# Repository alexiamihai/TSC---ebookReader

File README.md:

# OpenBook - Cititor ePaper cu ESP32-C6

## Prezentare

OpenBook este un eBook reader simplu si eficient, gandit pentru cei care vor o experienta de lectura fara distrageri. Proiectat in jurul microcontrollerului ESP32-C6, dispozitivul vine cu un ecran e-paper de 7.8 inch, ideal pentru afisarea clara a textelor in orice conditii de lumina.

Alimentarea se face printr-o baterie Li-Po de 3.7V, cu incarcare prin USB-C, iar navigarea printre pagini se realizeaza cu ajutorul butoanelor fizice, pentru o interactiune directa si intuitiva. In plus, cititorul dispune de un slot microSD pentru stocarea cartilor, un senzor BME680 pentru monitorizarea mediului si un LED pentru semnalizari vizuale.

Interfata este gandita sa fie cat mai clara si usor de folosit, controlata prin GPIO-uri, astfel incat sa te poti concentra pe ceea ce conteaza: lectura.

OpenBook este un dispozitiv compact, eficient energetic si usor de integrat in orice rutina de lectura zilnica.

## Caracteristici Tehnice

- **Controller principal**: ESP32-C6 (cu suport Wi-Fi 6, BLE si arhitectura RISC-V)
- **Display**: E-paper cu diagonala de 7.8"
- **Senzori inclusi**: BME680 - masoara temperatura, umiditate, presiune atmosferica si compusi gazosi
- **Alimentare**: Acumulator Li-Po 3.7V, reincarcabil prin USB-C
- **Timp real**: Ceas RTC extern pentru functionare in deep sleep
- **Control utilizator**: 3 butoane fizice + LED
- **Memorie externa**: microSD
- **Interfete disponibile**: USB-C si Qwiic

---

## Pasii de implementare

1. Realizarea schemei electronice.
2. Aranjarea componentelor pe placa PCB (2D)
3. Verificare ERC si DRC, corectarea erorilor aparute.
4. Rutare.
5. Decupaj sub antena ESP32 si eliminarea planului de masa din acea zona.
6. Proiectarea modelului tridimensional.
7. Integrarea PCB-ului intr-o carcasa 3D compatibila.
8. Realizarea bateriei si a display-ului.
9. Randare si simulare a prototipului final
---

## Estimare Consum Energetic

Mai jos sunt prezentate valorile medii de consum pentru principalele componente ale dispozitivului, atat in modul activ, cat si in repaus:

| Componenta            | Consum mediu            | Activ / Idle                         |
|----------------------|--------------------------|--------------------------------------|
| **ESP32-C6**         | ~80 mA                   | 130 mA activ / 12 µA in deep sleep   |
| **E-paper 7.8**     | ~26 mA in timpul refresh-ului | 0 mA in repaus                     |
| **Senzor BME680**    | ~2.1 mA                  | 0.15 mA in standby                   |
| **Card microSD**     | ~30-100 mA (in utilizare) | 0.1 mA in modul sleep               |
| **RTC + supercapacitor** | ~1 µA               | -                                    |
| **LED**              | max. ~10 mA              | Consumabil doar cand este activ     |

###  Total Estimat:
- **In utilizare activa**: ~100-150 mA
- **In modul deep sleep**: ~15 µA

###  Autonomie estimata (baterie 1200 mAh):
- **Utilizare activa, cu refresh ocazional**: aproximativ **8-10 ore**
- **Predominant in deep sleep**: pana la **300 de zile** in standby

##  Diagrame si Scheme

---

## Lista Componentelor (BOM)

# List of Components

Componentele utilizate in proiect sunt prezentate mai jos, alaturi de linkuri utile pentru verificarea preturilor si a fiselor tehnice. In cazurile in care nu a fost specificat un model exact, campurile corespunzatoare apar marcate cu **#N/A**.

| Name of component  | Device                                    | Check Prices                                                                 | DataSheet                                                                  |
|--------------------|-------------------------------------------|-----------------------------------------------------------------------------|----------------------------------------------------------------------------|
| BOOT_BUTTON        | BUTTON_CUSYOMV1                           | [Check Price](https://industry.panasonic.com/global/en/products/control/switch/light-touch/number/evqpuj02k)  | [DataSheet](https://industry.panasonic.com/global/en/products/control/switch/light-touch/number/evqpuj02k) |
| C1                 | ESP32_WROVER_EAGLE-LTSPICE_CC0402         | [Check Price](https://industry.panasonic.com/global/en/products/control/switch/light-touch/number/evqpuj02k)  | [DataSheet](https://industry.panasonic.com/global/en/products/control/switch/light-touch/number/evqpuj02k) |
| C1_BAT             | ESP32_WROVER_EAGLE-LTSPICE_CC0402         | #N/A                                                                         | #N/A                                                                      |
| C1_BAT1            | EAGLE-LTSPICE_CC0402                      | #N/A                                                                         | #N/A                                                                      |
| C1_BAT2            | EAGLE-LTSPICE_CC0402                      | #N/A                                                                         | #N/A                                                                      |
| C2                 | ESP32_WROVER_EAGLE-LTSPICE_CC0402         | #N/A                                                                         | #N/A                                                                      |
| C2_BAT\            | ESP32_WROVER_EAGLE-LTSPICE_CC0402         | #N/A                                                                         | #N/A                                                                      |
| C3                 | RCL_CPOL-EUCT3528                         | #N/A                                                                         | #N/A                                                                      |
| C4                 | ESP32_WROVER_EAGLE-LTSPICE_CC0402         | #N/A                                                                         | #N/A                                                                      |
| C4_USB             | ESP32_WROVER_EAGLE-LTSPICE_CC0402         | #N/A                                                                         | #N/A                                                                      |
| C5                 | ESP32_WROVER_EAGLE-LTSPICE_CC0402         | #N/A                                                                         | #N/A                                                                      |
| C5_USB             | ESP32_WROVER_EAGLE-LTSPICE_CC0402         | #N/A                                                                         | #N/A                                                                      |
| C6                 | ESP32_WROVER_EAGLE-LTSPICE_CC0402         | #N/A                                                                         | #N/A                                                                      |
| C7                 | ESP32_WROVER_EAGLE-LTSPICE_CC0402         | #N/A                                                                         | #N/A                                                                      |
| C8                 | ESP32_WROVER_EAGLE-LTSPICE_CC0402         | #N/A                                                                         | #N/A                                                                      |
| C9                 | EAGLE-LTSPICE_CC0402                      | #N/A                                                                         | #N/A                                                                      |
| C10                | ESP32_WROVER_EAGLE-LTSPICE_CC0402         | #N/A                                                                         | #N/A                                                                      |
| C10_SUPERCAP       | CPH3225A                                  | [Check Price](https://www.snapeda.com/parts/CPH3225A/Seiko+Instruments/view-part/?ref=eda) | [DataSheet](https://www.snapeda.com/parts/CPH3225A/Seiko+Instruments/view-part/?ref=eda) |
| CHANGE_BUTTON      | BUTTON_CUSYOMV1                           | [Check Price](https://industry.panasonic.com/global/en/products/control/switch-light-touch/number/evqpuj02k)  | [DataSheet](https://industry.panasonic.com/global/en/products/control/switch-light-touch/number/evqpuj02k) |
| CHG_LED            | ADAFRUIT_LEDCHIP-LED0603                  | [Check Price](https://www.snapeda.com/parts/KP-1608SURCK/Kingbright/view-part/?ref=search&t=LED%200603) | [DataSheet](https://www.snapeda.com/parts/KP-1608SURCK/Kingbright/view-part/?ref=search&t=LED%200603) |
| C_DELAY            | ESP32_WROVER_EAGLE-LTSPICE_CC0402         | #N/A                                                                         | #N/A                                                                      |
| D1                 | USBLC6-2SC6Y                              | [Check Price](https://www.snapeda.com/parts/USBLC6-2SC6Y/STMicroelectronics/view-part/?ref=eda) | [DataSheet](https://www.snapeda.com/parts/USBLC6-2SC6Y/STMicroelectronics/view-part/?ref=eda) |
| D2                 | ESP32_WROVER_AVX---SD0805S020S1R0_AVX_... | [Check Price](https://eu.mouser.com/ProductDetail/KYOCERA-AVX/SD0805S020S1R0?qs=jCA%252BPfw4LHbpkAoSnwrdjw%3D%3D) | [DataSheet](http://datasheets.avx.com/schottky.pdf)                       |
| D3                 | MBR0530                                   | [Check Price](https://eu.mouser.com/ProductDetail/KYOCERA-AVX/SD0805S020S1R0?qs=jCA%252BPfw4LHbpkAoSnwrdjw%3D%3D) | [DataSheet](https://eu.mouser.com/ProductDetail/KYOCERA-AVX/SD0805S020S1R0?qs=jCA%252BPfw4LHbpkAoSnwrdjw%3D%3D) |
| D4                 | MBR0530                                   | [Check Price](https://www.snapeda.com/parts/MBR0530/Onsemi/view-part/?ref=eda) | [DataSheet](https://www.snapeda.com/parts/MBR0530/Onsemi/view-part/?ref=eda) |
| D5                 | MBR0530                                   | [Check Price](https://www.snapeda.com/parts/MBR0530/Onsemi/view-part/?ref=eda) | [DataSheet](https://www.snapeda.com/parts/MBR0530/Onsemi/view-part/?ref=eda) |
| D6                 | PGB1010603MR                              | [Check Price](https://www.snapeda.com/parts/PGB1010603MR/Littelfuse/view-part/?ref=eda) | [DataSheet](https://www.snapeda.com/parts/PGB1010603MR/Littelfuse/view-part/?ref=eda) |
| D7                 | ESP32_WROVER_AVX---SD0805S020S1R0_AVX_... | [Check Price](https://eu.mouser.com/ProductDetail/KYOCERA-AVX/SD0805S020S1R0?qs=jCA%252BPfw4LHbpkAoSnwrdjw%3D%3D) | [DataSheet](http://datasheets.avx.com/schottky.pdf)                       |
| D8                 | PGB1010603MR                              | [Check Price](https://www.snapeda.com/parts/PGB1010603MR/Littelfuse/view-part/?ref=eda) | [DataSheet](https://www.snapeda.com/parts/PGB1010603MR/Littelfuse/view-part/?ref=eda) |
| D9                 | PGB1010603MR                              | [Check Price](https://www.snapeda.com/parts/PGB1010603MR/Littelfuse/view-part/?ref=eda) | [DataSheet](https://www.snapeda.com/parts/PGB1010603MR/Littelfuse/view-part/?ref=eda) |
| D10                | PGB1010603MR                              | [Check Price](https://www.snapeda.com/parts/PGB1010603MR/Littelfuse/view-part/?ref=eda) | [DataSheet](https://www.snapeda.com/parts/PGB1010603MR/Littelfuse/view-part/?ref=eda) |
| D11                | PGB1010603MR                              | [Check Price](https://www.snapeda.com/parts/PGB1010603MR/Littelfuse/view-part/?ref=eda) | [DataSheet](https://www.snapeda.com/parts/PGB1010603MR/Littelfuse/view-part/?ref=eda) |
| D12                | PGB1010603MR                              | [Check Price](https://www.snapeda.com/parts/PGB1010603MR/Littelfuse/view-part/?ref=eda) | [DataSheet](https://www.snapeda.com/parts/PGB1010603MR/Littelfuse/view-part/?ref=eda) |
| EPD_C1             | ESP32_WROVER_EAGLE-LTSPICE_CC0402         | #N/A                                                                         | #N/A                                                                      |
| EPD_C2             | ESP32_WROVER_EAGLE-LTSPICE_CC0402         | #N/A                                                                         | #N/A                                                                      |
| EPD_C5             | ESP32_WROVER_EAGLE-LTSPICE_CC0402         | #N/A                                                                         | #N/A                                                                      |
| EPD_C6             | ESP32_WROVER_EAGLE-LTSPICE_CC0402         | #N/A                                                                         | #N/A                                                                      |
| EPD_C7             | ESP32_WROVER_EAGLE-LTSPICE_CC0402         | #N/A                                                                         | #N/A                                                                      |
| EPD_C8             | ESP32_WROVER_EAGLE-LTSPICE_CC0402         | #N/A                                                                         | #N/A                                                                      |
| EPD_C9             | ESP32_WROVER_EAGLE-LTSPICE_CC0402         | #N/A                                                                         | #N/A                                                                      |
| EPD_C10            | ESP32_WROVER_EAGLE-LTSPICE_CC0402         | #N/A                                                                         | #N/A                                                                      |
| EPD_C11            | ESP32_WROVER_EAGLE-LTSPICE_CC0402         | #N/A                                                                         | #N/A                                                                      |
| EPD_C12            | ESP32_WROVER_EAGLE-LTSPICE_CC0402         | #N/A                                                                         | #N/A                                                                      |
| IC1                | BD5229G-TR                                | [Check Price](https://componentsearchengine.com/part-view/BD5229G-TR/ROHM%20Semiconductor) | [DataSheet](https://componentsearchengine.com/part-view/BD5229G-TR/ROHM%20Semiconductor) |
| IC4                | XC6220A331MR-G                            | [Check Price](https://componentsearchengine.com/part-view/XC6220A331MR-G/Torex) | [DataSheet](https://componentsearchengine.com/part-view/XC6220A331MR-G/Torex) |
| J1                 | FH34SRJ-24S-0.5SH_99_                     | [Check Price](https://componentsearchengine.com/part-view/XC6220A331MR-G/Torex) | [DataSheet](https://componentsearchengine.com/part-view/XC6220A331MR-G/Torex) |
| J2                 | SAMACSYS_PARTS_USB4110-GF-A               | [Check Price](https://componentsearchengine.com/part-view/USB4110-GF-A/GCT%20(GLOBAL%20CONNECTOR%20TECHNOLOGY)) | [DataSheet](https://componentsearchengine.com/part-view/USB4110-GF-A/GCT%20(GLOBAL%20CONNECTOR%20TECHNOLOGY)) |
| J3                 | QWIIC_CONNECTORJS-1MM                     | #N/A                                                                         | #N/A                                                                      |
| J4                 | 112A-TAAR-R03_ATTEND                      | [Check Price](https://store.comet.srl.ro/Catalogue/Product/43497/)           | [DataSheet](https://store.comet.srl.ro/Catalogue/Product/43497/)          |
| L1                 | 744043680IND_4828-WE-TPC_WRE              | [Check Price](https://eu.mouser.com/ProductDetail/Wurth-Elektronik/744043680?qs=PGXP4M47uW6VkZq%252BkzjrHA%3D%3D) | [DataSheet](https://eu.mouser.com/ProductDetail/Wurth-Elektronik/744043680?qs=PGXP4M47uW6VkZq%252BkzjrHA%3D%3D) |
| PFMF.050.1         | ESP32C6_VARISTORCN1812                    | [Check Price](https://www.mouser.co.uk/ProductDetail/EPCOS-TDK/B72520T0350K062?qs=dEfas%2FXlABIszF52uu7vrg%3D%3D) | [DataSheet](https://www.mouser.co.uk/ProductDetail/EPCOS-TDK/B72520T0350K062?qs=dEfas%2FXlABIszF52uu7vrg%3D%3D) |
| Q1                 | ESP32_WROVER_SPARKFUN-DISCRETESEMI_MOSFET_... | [Check Price](https://componentsearchengine.com/part-view/DMG2305UX-7/Diodes%20Incorporated) | [DataSheet](https://componentsearchengine.com/part-view/DMG2305UX-7/Diodes%20Incorporated) |
| Q2                 | ESP32_WROVER_SPARKFUN-DISCRETESEMI_MOSFET_... | #N/A                                                                         | #N/A                                                                      |
| Q3                 | D8                                        | [Check Price](https://componentsearchengine.com/part-view/PGB1010603MR/Littelfuse) | [DataSheet](https://componentsearchengine.com/part-view/PGB1010603MR/Littelfuse) |
| Q4                 | Q2_TS-B2_REACHPACK                        | #N/A                                                                         | #N/A                                                                      |

### Descrierea hardware -- Conexiuni si Functionalitate

1.  **USB-C Connector & ESD Protection**\
    Conectorul USB-C permite atat programarea ESP32-C6, cat si incarcarea bateriei prin VBUS. Se conecteaza la MCP73831 pentru incarcarea bateriei si la ESP32-C6 pentru programare. Pinii ESP32-C6 implicati sunt IO13 (USB_D-) si IO14 (USB_D+).

2.  **Li-Po Battery + MCP73831 (Battery Charging Controller)**\
    Bateria Li-Po este gestionata de MCP73831 pentru incarcare si furnizarea de energie intregului sistem. MCP73831 este conectat la un regulator LDO care asigura tensiunea de 3.3V pentru ESP32-C6. LED-ul de incarcare este controlat de pinul IO4.

3.  **XC6220 (LDO Voltage Regulator)**\
    Regulatorul de tensiune LDO asigura o tensiune stabila de 3.3V, esentiala pentru functionarea corecta a componentelor digitale. Se conecteaza la MCP73831 si furnizeaza alimentare la ESP32-C6.

4.  **W25Q512 (External NOR Flash)**\
    Memoria flash externa W25Q512 este utilizata pentru stocarea datelor persistente. Este conectata la ESP32-C6 prin SPI, avand pini pentru semnalul de ceas (SCK), datele de iesire (MOSI), datele de intrare (MISO) si selectarea chipului (CS).

5.  **E-Paper Display Header & Driver**\
    Ecranul e-paper este controlat prin SPI, avand semnale suplimentare pentru controlul de stare. Pinii IO6, IO7 si IO2 sunt folositi pentru comunicarea SPI, iar pini suplimentari sunt utilizati pentru semnalele de comanda (DC), ocupare (BUSY) si resetare (RST).

6.  **MicroSD Card**\
    Cardul microSD este folosit pentru stocarea de fisiere externe, cum ar fi texte sau resurse. Foloseste aceleasi pini SPI partajati cu alte periferice (SCK, MOSI, MISO), cu un pin dedicat pentru selectarea cardului (CS_SD).

7.  **RTC DS3231SN**\
    Ceasul RTC DS3231SN ofera o masuratoare precisa a timpului, chiar si in modul de repaus al ESP32-C6. Acesta este conectat la ESP32-C6 prin I2C si include pini pentru intreruperi (INT_RTC) si reset (RTC_RST), permitand trezirea automata a sistemului.

8.  **BME680 -- Environmental Sensor**\
    Senzorul BME680 masoara temperatura, umiditatea, presiunea si calitatea aerului. Acesta este conectat la ESP32-C6 prin I²C, avand pini partajati cu RTC pentru comunicarea datelor.

9.  **Butoane de control (BOOT, CHANGE, RESET)**\
    Butoanele de control permit utilizatorului sa interactioneze cu sistemul. Pinul BOOT (IO15) este folosit pentru programare, pinul RESET (IO3) pentru a reseta sistemul, iar pinul CHANGE (IO23) permite schimbarea optiunilor sau navigarea prin interfata.

10. **Voltage Supervisor & IO**\
    Supraveghetorul de tensiune monitorizeaza tensiunile critice si protejeaza sistemul in timpul pornirii si resetarii. Acesta este conectat la pinul IO1, IO18 si IO22 de pe ESP32-C6, asigurand functionarea corecta a circuitului.

11. **Battery Level Monitor**\
    Monitorizarea nivelului bateriei se realizeaza prin intermediul unui pin ADC (IO18) care masoara tensiunea bateriei. Aceste informatii sunt folosite pentru a trimite notificari utilizatorului sau pentru a inregistra nivelul bateriei.

12. **Qwiic / Stemma QT Connector**\
    Conectorul Qwiic / Stemma QT permite extinderea sistemului prin adaugarea de senzori I2C suplimentari, fara a necesita lipirea firelor. Acesta este conectat la ESP32-C6 prin pini I2C(SDA si SCL).

13. **Serial (TX/RX)**\
    Conexiunea seriala UART (TX/RX) este folosita pentru debug si comunicare intre ESP32-C6 si un PC sau terminal. Pinul TX (IO25) trimite date catre PC, iar pinul RX (IO24) primeste date de la PC.

### Pinout ESP32-C6

1.  **IO2 -- MISO (SPI)**\
    Acest pin este utilizat pentru comunicarea SPI, fiind dedicat transferului de date catre microcontroller dinspre perifericele externe, cum ar fi Flash NOR, E-Paper si microSD. Asigura viteza si compatibilitate nativa pentru aceste dispozitive.

2.  **IO6 -- SCK (SPI Clock)**\
    Pinul IO6 este folosit ca semnal de ceas (SCK) in protocolul SPI, esential pentru sincronizarea transferurilor de date. Este recomandat pentru a partaja magistrala SPI intre diferite periferice, precum Flash NOR, E-Paper si microSD.

3.  **IO7 -- MOSI (SPI Data Out)**\
    Acest pin transmite date catre perifericele conectate prin SPI. Este folosit de dispozitivele Flash NOR, E-Paper si microSD pentru a primi informatiile necesare, oferind o comunicatie rapida.

4.  **IO4 -- CS_SD**\
    Pinul CS_SD selecteaza cardul microSD pentru citirea datelor. Utilizarea acestui pin permite evitarea conflictelor cu alte periferice SPI, asigurand o accesibilitate exclusiva la cardul SD in timpul operatiunii de citire sau scriere.

5.  **IO12 -- CS Flash**\
    Acest pin este utilizat pentru a activa memoria Flash externa. Este dedicat selectarii si initializarii memoriei NOR Flash, permitand un acces rapid si sigur la stocarea externa.

6.  **IO10 -- CS EPD**\
    Pinul CS EPD este folosit pentru a selecta afisajul E-Paper in timpul transferurilor de date prin SPI. Asigura ca ecranul este adresabil si se poate comunica cu el in mod eficient.

7.  **IO5 -- DC (Data/Command pentru EPD)**\
    Semnalul DC controleaza diferentierea intre comenzi si date in cazul afisajului E-Paper. Acest pin permite gestionarea corecta a fluxului de informatii intre microcontroller si ecran.

8.  **IO14 -- EPD_BUSY**\
    Pinul EPD_BUSY este un semnal de stare care indica daca ecranul E-Paper este ocupat. Permite sistemului sa astepte finalizarea operatiunilor curente ale ecranului inainte de a trimite noi comenzi.

9.  **IO21 -- EPD_RST**\
    Acest pin este utilizat pentru a reseta afisajul E-Paper inainte de initializarea sa. Este important pentru a asigura o pornire corecta si o performanta optima a display-ului.

10. **IO19 -- SDA (I2C)**\
    Pinul SDA face parte din magistrala I2C si este utilizat de senzori precum RTC, BME680 si Qwiic pentru a trimite si primi date. Acesta este partajat intre mai multi senzori, permitand comunicarea eficienta.

11. **IO20 -- SCL (I2C)**\
    Pinul SCL este linia de ceas in protocolul I2C, sincronizand comunicatiile dintre dispozitivele conectate la magistrala I2C, inclusiv RTC si BME680.

12. **IO0 -- INT RTC**\
    Acest pin este un semnal de intrerupere care permite ESP32-C6 sa trezeasca din starea de deep sleep atunci cand RTC detecteaza un eveniment semnificativ, precum un schimb de timp sau o alarma.

13. **IO17 -- RTC Reset**\
    Pinul RTC Reset este folosit pentru a efectua un reset extern al RTC (Real Time Clock). Acest pin asigura sincronizari initiale corecte pentru ceasul RTC, garantand acuratetea masuratorilor de timp.

14. **IO15 -- BOOT**\
    Pinul BOOT este utilizat pentru a introduce ESP32-C6 in modul de programare. Acesta permite incarcarea unui firmware nou pe microcontroller.

15. **IO3 -- RESET**\
    Pinul RESET permite resetarea manuala a microcontrollerului ESP32-C6. Acesta poate fi folosit pentru a reporni sistemul in caz de erori sau modificari ale configurarii.

16. **IO23 -- Buton CHANGE**\
    Pinul IO23 este folosit pentru un buton de schimbare in interfata utilizatorului. Acesta poate fi utilizat pentru a naviga prin optiuni sau a schimba paginile in aplicatii.

17. **IO25/IO24 -- UART TX/RX**\
    Pinii IO25 si IO24 sunt folositi pentru comunicatia seriala UART. Acestia permit ESP32-C6 sa comunice cu un PC sau terminal pentru debug si monitorizare.

18. **IO18 -- Battery Monitor**\
    Pinul IO18 este folosit pentru monitorizarea nivelului bateriei prin intermediul unui ADC (Analog-to-Digital Converter). Acest pin masoara tensiunea bateriei, permitand sistemului sa notifice utilizatorul sau sa inregistreze datele pentru analize ulterioare.

### Concluzie

Extrem de stresant, dar macar s-a terminat. Sper ca totul e okay. Slay!

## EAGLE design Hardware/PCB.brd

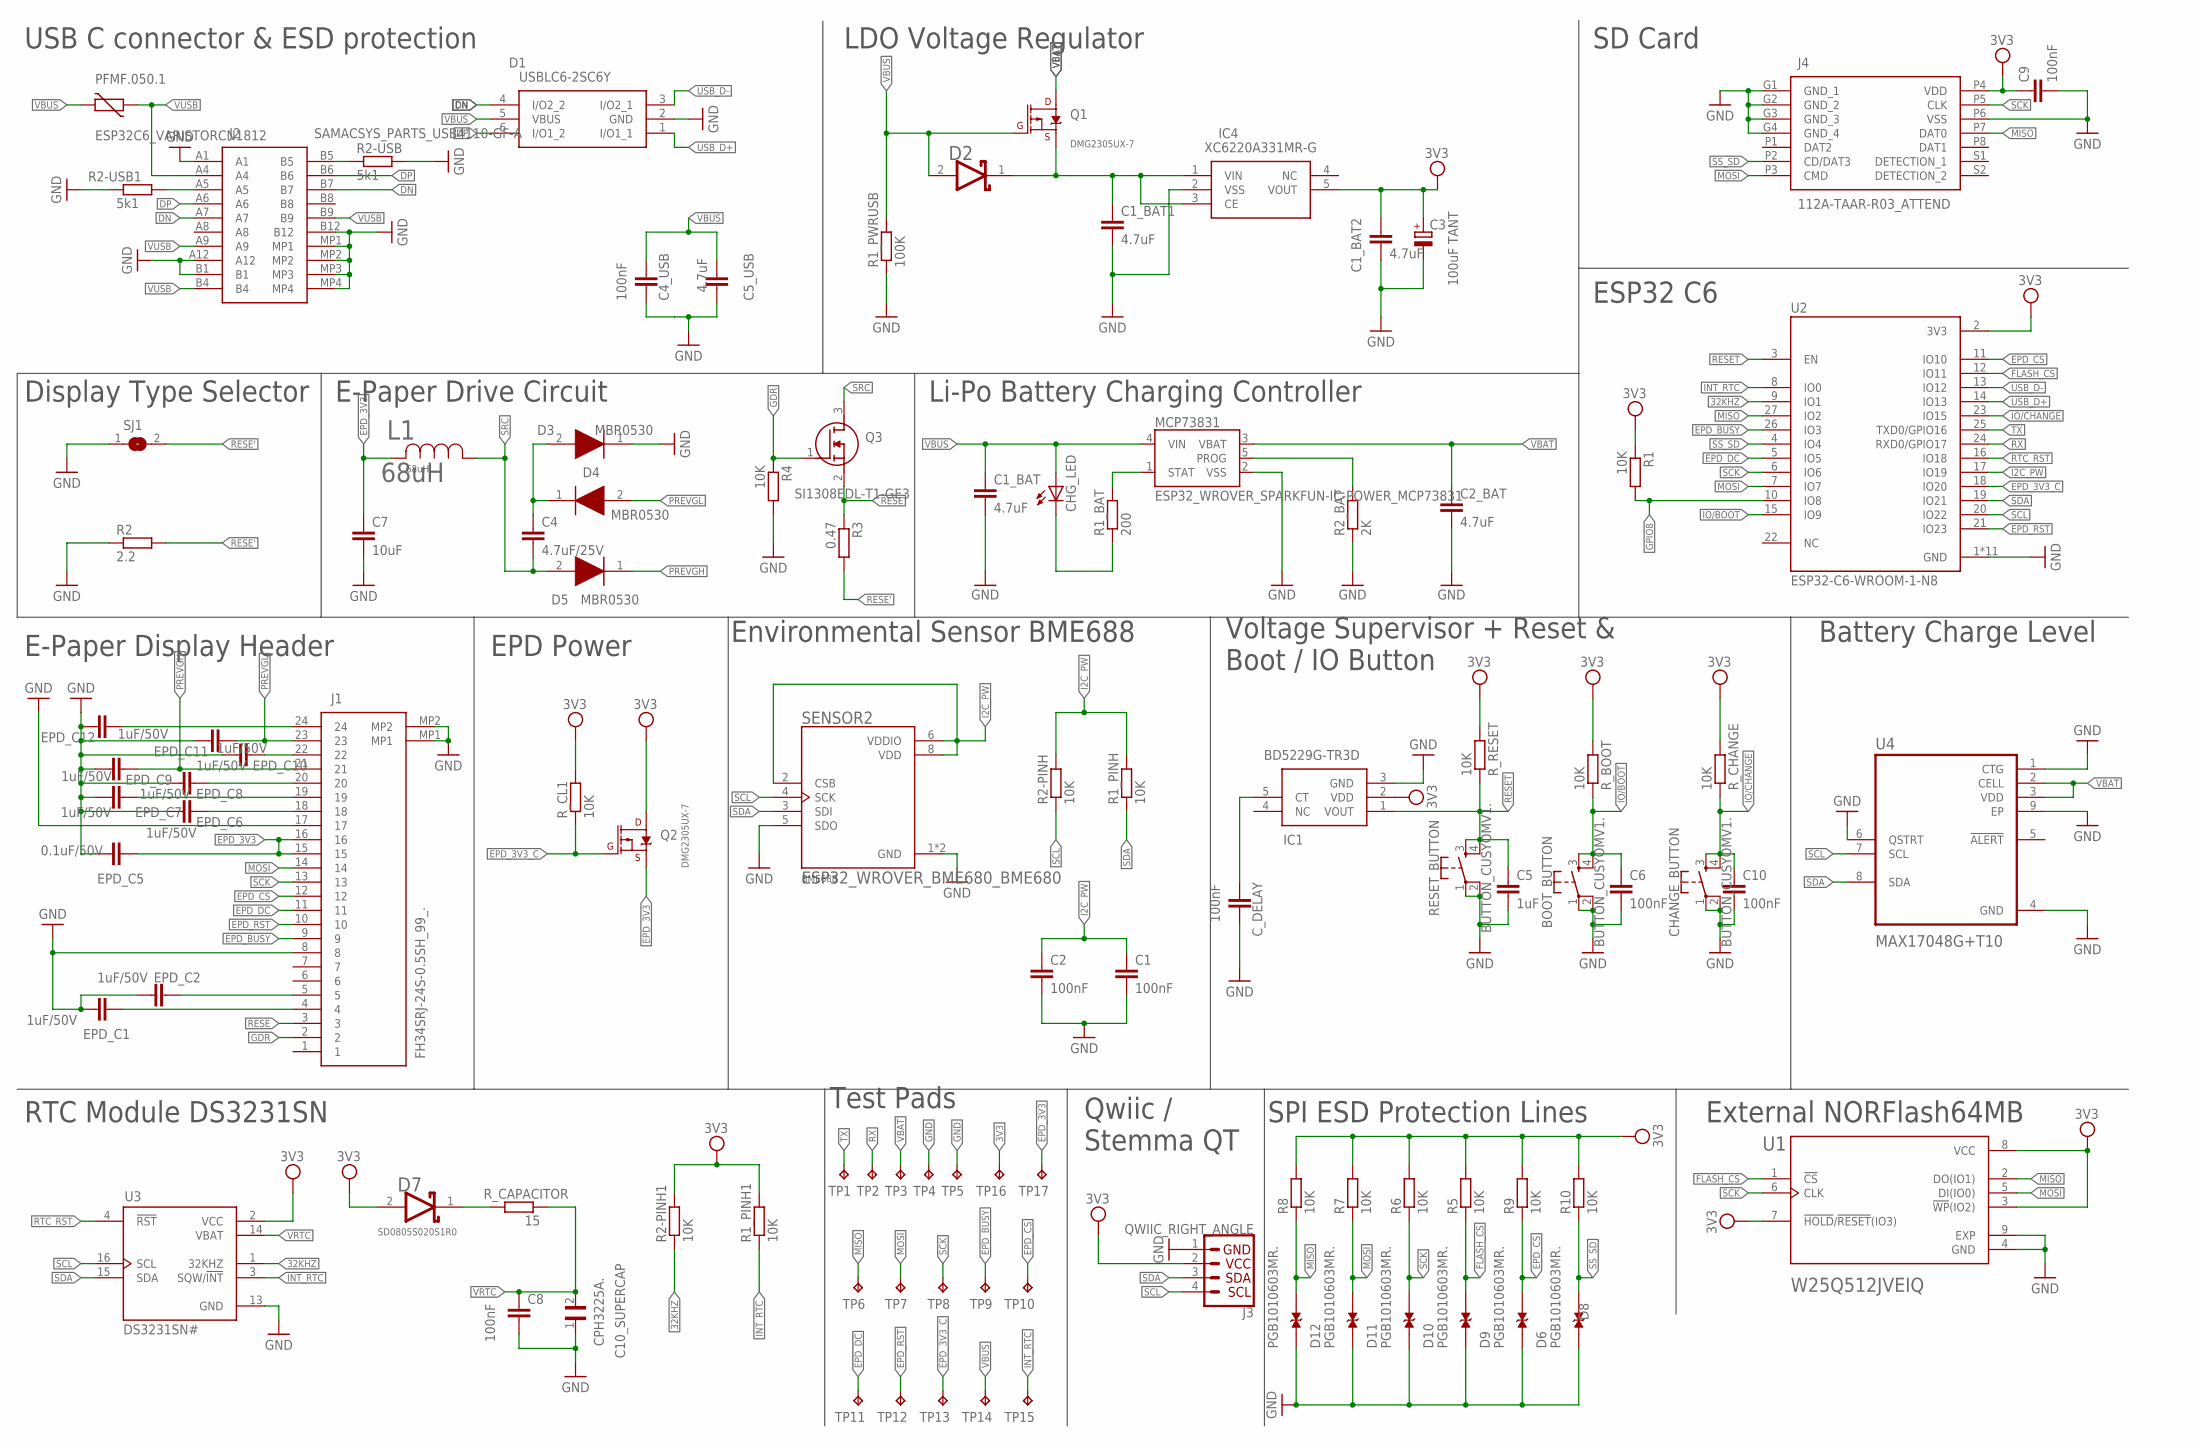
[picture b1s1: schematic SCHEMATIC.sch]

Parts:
BOOT_BUTTON: BUTTON_CUSYOMV1.; MYBUTTON
C1, C2, C4_USB, C6, C8, C9, C10: 100nF; EAGLE-LTSPICE_C0402
C1_BAT, C1_BAT1, C1_BAT2, C2_BAT, C5_USB: 4.7uF; EAGLE-LTSPICE_C0402
C3: 100uF TANT; RCL_CT3528
C4: 4.7uF/25V; EAGLE-LTSPICE_C0402
C5: 1uF; EAGLE-LTSPICE_C0402
C7: 10uF; EAGLE-LTSPICE_C0402
C10_SUPERCAP: CPH3225A.; CAPCP3225X100N
CHANGE_BUTTON: BUTTON_CUSYOMV1.; MYBUTTON
CHG_LED: ADAFRUIT_LEDCHIP-LED0603; ADAFRUIT_CHIP-LED0603
C_DELAY: 100nF; EAGLE-LTSPICE_C0402
D1: USBLC6-2SC6Y; SOT95P280X145-6N
D2, D7: ESP32_WROVER_AVX---SD0805S020S1R0_AVX_SD0805S020S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; ESP32_WROVER_AVX---SD0805S020S1R0_AVX_SD0805S020S1R0_0
D3, D4, D5: MBR0530; SOD3716X135N
D6, D8, D9, D10, D11, D12: PGB1010603MR.; DIOC1608X36N
EPD_C1, EPD_C2, EPD_C6, EPD_C7, EPD_C8, EPD_C9, EPD_C10, EPD_C11, EPD_C12: 1uF/50V; EAGLE-LTSPICE_C0402
EPD_C5: 0.1uF/50V; EAGLE-LTSPICE_C0402
IC1: BD5229G-TR3D; SOT95P280X125-5N
IC4: XC6220A331MR-G; SOT95P280X120-5N
J1: FH34SRJ-24S-0.5SH_99_.; FH34SRJ24S05SH99
J2: SAMACSYS_PARTS_USB4110-GF-A; SAMACSYS_PARTS_USB4110GFA
J3: QWIIC_RIGHT_ANGLE; JST04_1MM_RA
J4: 112A-TAAR-R03_ATTEND; 112ATAARR03ATTEND
L1: 68uH; IND_4828-WE-TPC_WRE
MCP73831: ESP32_WROVER_SPARKFUN-IC-POWER_MCP73831; ESP32_WROVER_SPARKFUN-IC-POWER_SOT23-5
PFMF.050.1: ESP32C6_VARISTORCN1812; ESP32C6_VARISTOR_CT/CN1812
Q1, Q2: 20V/4.2A/52mΩ/1.4W; ESP32_WROVER_SPARKFUN-DISCRETESEMI_SOT23-3
Q3: SI1308EDL-T1-GE3; SOT65P210X110-3N
R1, R1_PINH, R1_PINH1, R2-PINH, R2-PINH1, R4, R5, R6, R7, R8, R9, R10: 10K; ESP32_WROVER_EAGLE-LTSPICE_R0402
R1_BAT: 200; ESP32_WROVER_EAGLE-LTSPICE_R0402
R1_PWRUSB: 100K; ESP32_WROVER_EAGLE-LTSPICE_R0402
R2: 2.2; ESP32_WROVER_EAGLE-LTSPICE_R0402
R2-USB, R2-USB1: 5k1; ESP32_WROVER_EAGLE-LTSPICE_R0402
R2_BAT: 2K; ESP32_WROVER_EAGLE-LTSPICE_R0402
R3: 0.47; ESP32_WROVER_EAGLE-LTSPICE_R0402
RESET_BUTTON: BUTTON_CUSYOMV1.; MYBUTTON
R_BOOT: 10K; ESP32_WROVER_EAGLE-LTSPICE_R0402
R_CAPACITOR: 15; ESP32_WROVER_EAGLE-LTSPICE_R0402
R_CHANGE: 10K; ESP32_WROVER_EAGLE-LTSPICE_R0402
R_CL1: 10K; ESP32_WROVER_EAGLE-LTSPICE_R0402
R_RESET: 10K; ESP32_WROVER_EAGLE-LTSPICE_R0402
SENSOR2: ESP32_WROVER_BME680_BME680; ESP32_WROVER_BME680_PSON80P300X300X100-8N
SJ1: SJ.; SJ
TP1, TP2, TP3, TP4, TP5, TP6, TP7, TP8, TP9, TP10, TP11, TP12, TP13, TP14, TP15, TP16, TP17: TPTP20R; TP20R
U1: W25Q512JVEIQ; SON127P600X800X80-9N
U2: ESP32-C6-WROOM-1-N8; XCVR_ESP32-C6-WROOM-1-N8
U3: DS3231SN#; SOIC127P1032X265-16N
U4: MAX17048G+T10; SON50P200X200X80-9N

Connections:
3V3: C1_BAT2.1, C3.+, C9.1, D7.2 (ANODE), IC1.2 (VDD), IC4.5 (VOUT), J3.2, J4.P4 (VDD), Q2.3 (D), R1.1, R1_PINH1.2, R2-PINH1.2, R5.2, R6.2, R7.2, R8.2, R9.2, R10.2, R_BOOT.2, R_CHANGE.2, R_CL1.2, R_RESET.2, TP16.TP, U1.3 (!WP!(IO2)), U1.7 (!HOLD!/!RESET!(IO3)), U1.8 (VCC), U2.2 (3V3), U3.2 (VCC)
32KHZ: R2-PINH1.1, U2.9 (IO1), U3.1 (32KHZ)
DN: D1.4 (I/O2_2), J2.A7, J2.B7
DP: D1.6 (I/O1_2), J2.A6, J2.B6
EPD_3V3: C7.1, EPD_C5.1, J1.15, J1.16, L1.2, Q2.2 (S), TP17.TP
EPD_3V3_C: Q2.1 (G), R_CL1.1, TP13.TP, U2.18 (IO20)
EPD_BUSY: J1.9, TP9.TP, U2.26 (IO3)
EPD_CS: D6.2, J1.12, R9.1, TP10.TP, U2.11 (IO10)
EPD_DC: J1.11, TP11.TP, U2.5 (IO5)
EPD_RST: J1.10, TP12.TP, U2.21 (IO23)
FLASH_CS: D9.2, R5.1, U1.1 (!CS), U2.12 (IO11)
GDR: J1.2, Q3.1 (G), R4.1
GND: BOOT_BUTTON.1, BOOT_BUTTON.2, C1.2, C1_BAT.2, C1_BAT1.2, C1_BAT2.2, C2.2, C2_BAT.2, C3.-, C4_USB.2, C5.2, C5_USB.2, C6.2, C7.2, C8.2, C9.2, C10.2, C10_SUPERCAP.1, CHANGE_BUTTON.1, CHANGE_BUTTON.2, C_DELAY.2, D1.2 (GND), D3.1 (K), D6.1, D8.1, D9.1, D10.1, D11.1, D12.1, EPD_C1.2, EPD_C2.2, EPD_C5.2, EPD_C6.2, EPD_C7.2, EPD_C8.2, EPD_C9.2, EPD_C10.2, EPD_C11.2, EPD_C12.2, IC1.3 (GND), IC4.2 (VSS), J1.8, J1.17, J1.MP1, J1.MP2, J2.A1, J2.A12, J2.B1, J2.B12, J2.MP1, J2.MP2, J2.MP3, J2.MP4, J3.1, J4.G1 (GND_1), J4.G2 (GND_2), J4.G3 (GND_3), J4.G4 (GND_4), J4.P6 (VSS), MCP73831.2 (VSS), R1_PWRUSB.1, R2.1, R2-USB.2, R2-USB1.1, R2_BAT.1, R4.2, RESET_BUTTON.1, RESET_BUTTON.2, SENSOR2.1 (GND), SENSOR2.5 (SDO), SENSOR2.7 (GND), SJ1.1, TP4.TP, TP5.TP, U1.4 (GND), U1.9 (EXP), U2.1 (GND), U2.28 (GND), U2.29_1 (GND), U2.29_2 (GND), U2.29_3 (GND), U2.29_4 (GND), U2.29_5 (GND), U2.29_6 (GND), U2.29_7 (GND), U2.29_8 (GND), U2.29_9 (GND), U3.13 (GND), U4.1 (CTG), U4.4 (GND), U4.6 (QSTRT), U4.9 (EP)
GPIO8: R1.2, U2.10 (IO8)
I2C_PW: C1.1, C2.1, R1_PINH.2, R2-PINH.2, SENSOR2.2 (CSB), SENSOR2.6 (VDDIO), SENSOR2.8 (VDD), U2.17 (IO19)
INT_RTC: R1_PINH1.1, TP15.TP, U2.8 (IO0), U3.3 (SQW/!INT)
IO/BOOT: BOOT_BUTTON.3, BOOT_BUTTON.4, C6.1, R_BOOT.1, U2.15 (IO9)
IO/CHANGE: C10.1, CHANGE_BUTTON.3, CHANGE_BUTTON.4, R_CHANGE.1, U2.23 (IO15)
MISO: D12.2, J4.P7 (DAT0), R8.1, TP6.TP, U1.2 (DO(IO1)), U2.27 (IO2)
MOSI: D11.2, J1.14, J4.P3 (CMD), R7.1, TP7.TP, U1.5 (DI(IO0)), U2.7 (IO7)
unnamed: C_DELAY.1, IC1.5 (CT)
unnamed: EPD_C12.1, J1.24
unnamed: CHG_LED.C, R1_BAT.1
unnamed: EPD_C6.1, J1.18
unnamed: D7.1 (CATHODE), R_CAPACITOR.2
unnamed: EPD_C8.1, J1.20
unnamed: EPD_C1.1, J1.4
unnamed: MCP73831.1 (STAT), R1_BAT.2
unnamed: MCP73831.5 (PROG), R2_BAT.2
unnamed: C4.1, D3.2 (A), D4.1 (K)
unnamed: EPD_C2.1, J1.5
unnamed: EPD_C7.1, J1.19
unnamed: EPD_C10.1, J1.22
unnamed: C1_BAT1.1, D2.1 (CATHODE), IC4.1 (VIN), IC4.3 (CE), Q1.2 (S)
unnamed: J2.A5, R2-USB1.2
unnamed: J2.B5, R2-USB.1
PREVGH: D5.1 (K), EPD_C9.1, J1.21
PREVGL: D4.2 (A), EPD_C11.1, J1.23
RESE: J1.3, Q3.2 (S), R3.1
RESE': R2.2, R3.2, SJ1.2
RESET: C5.1, IC1.1 (VOUT), RESET_BUTTON.3, RESET_BUTTON.4, R_RESET.1, U2.3 (EN)
RTC_RST: U2.16 (IO18), U3.4 (!RST)
RX: TP2.TP, U2.24 (RXD0/GPIO17)
SCK: D10.2, J1.13, J4.P5 (CLK), R6.1, TP8.TP, U1.6 (CLK), U2.6 (IO6)
SCL: J3.4, R2-PINH.1, SENSOR2.4 (SCK), U2.20 (IO22), U3.16 (SCL), U4.7 (SCL)
SDA: J3.3, R1_PINH.1, SENSOR2.3 (SDI), U2.19 (IO21), U3.15 (SDA), U4.8 (SDA)
SRC: C4.2, D5.2 (A), L1.1, Q3.3 (D)
SS_SD: D8.2, J4.P2 (CD/DAT3), R10.1, U2.4 (IO4)
TX: TP1.TP, U2.25 (TXD0/GPIO16)
USB_D+: D1.1 (I/O1_1), U2.14 (IO13)
USB_D-: D1.3 (I/O2_1), U2.13 (IO12)
VBAT: C2_BAT.1, MCP73831.3 (VBAT), Q1.3 (D), TP3.TP, U4.2 (CELL), U4.3 (VDD)
VBUS: C1_BAT.1, C4_USB.1, C5_USB.1, CHG_LED.A, D1.5 (VBUS), D2.2 (ANODE), MCP73831.4 (VIN), PFMF.050.1.2, Q1.1 (G), R1_PWRUSB.2, TP14.TP
VRTC: C8.1, C10_SUPERCAP.2, R_CAPACITOR.1, U3.14 (VBAT)
VUSB: J2.A4, J2.A9, J2.B4, J2.B9, PFMF.050.1.1

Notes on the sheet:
SD Card
ESP32 C6
Battery Charge Level
USB C connector & ESD protection
LDO Voltage Regulator
Display Type Selector
E-Paper Drive Circuit
Li-Po Battery Charging Controller
E-Paper Display Header
EPD Power
Environmental Sensor BME688
Voltage Supervisor + Reset & Boot / IO Button
RTC Module DS3231SN
Test Pads
Qwiic / Stemma QT
SPI ESD Protection Lines
External NORFlash64MB

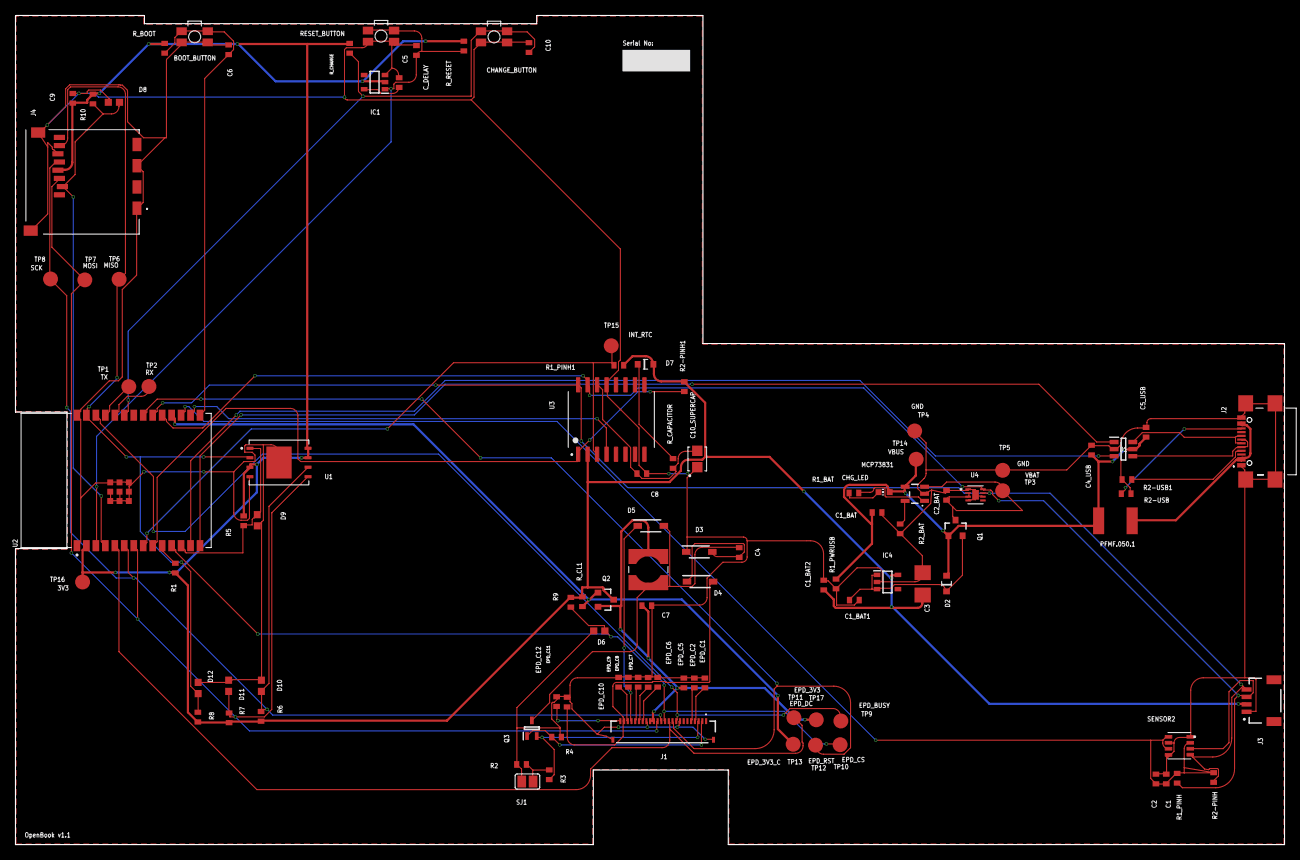
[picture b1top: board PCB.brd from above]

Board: 2 copper layers, 170.2 x 111.2 mm, 103 parts (0 on the bottom side), 55 nets.

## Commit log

2025-04-05 Create LICENSE
2025-04-05 Create a
